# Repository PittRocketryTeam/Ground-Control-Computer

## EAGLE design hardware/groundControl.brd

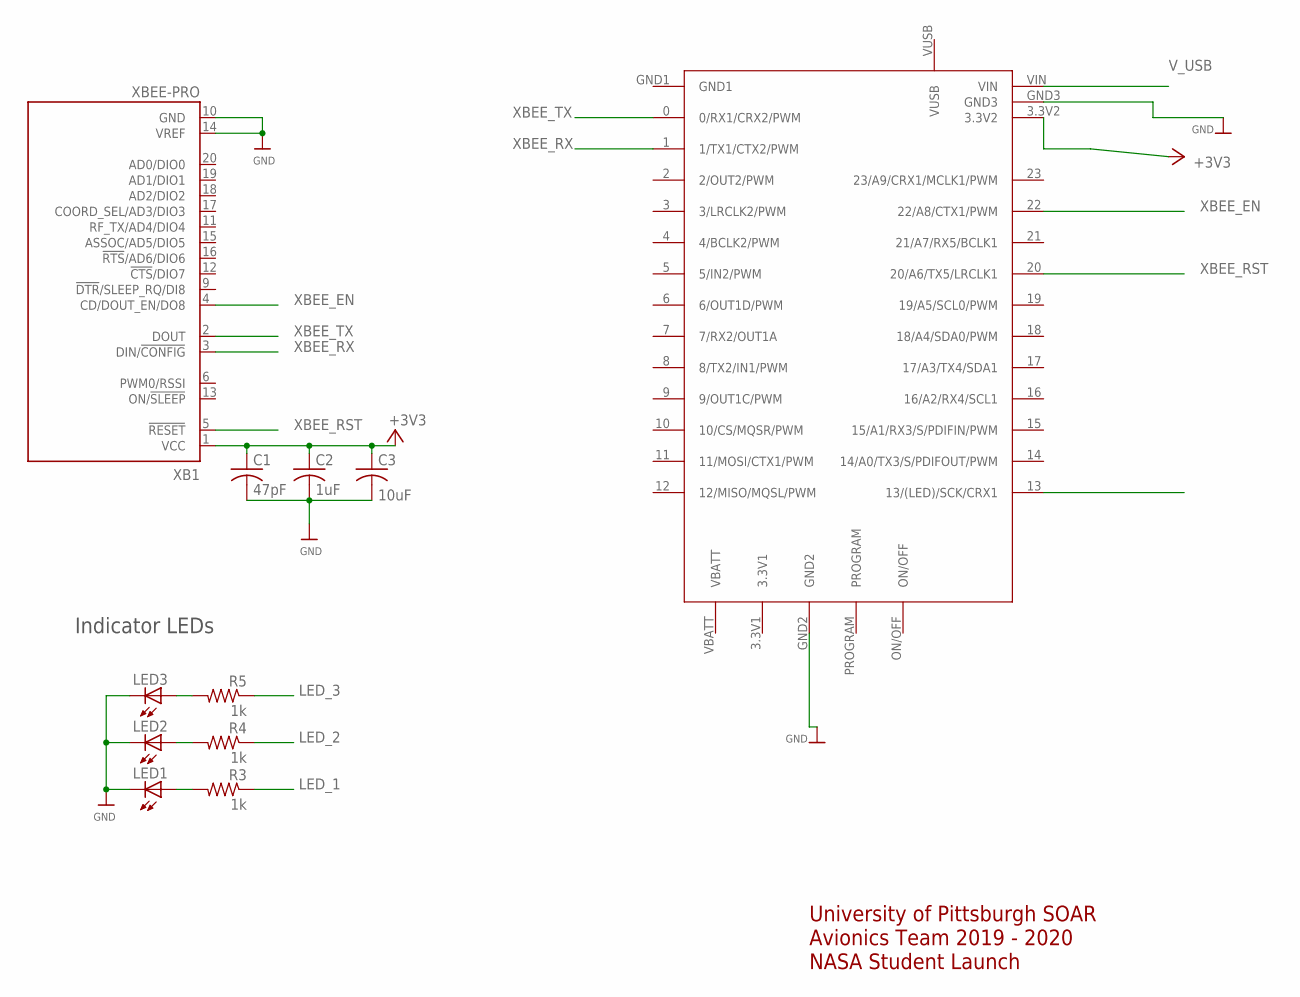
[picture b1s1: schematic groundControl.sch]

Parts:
C1: 47pF; C025-040X050
C2: 1uF; C025-040X050
C3: 10uF; C025-040X050
LED1, LED2, LED3: LED3MM
R3, R4, R5: 1k; 0309/10
U$3: TEENSY4.0
XB1: XBEE-PRO

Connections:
+3V3: C1.1, C2.1, C3.1, U$3.3.3V2, XB1.1 (VCC); also elsewhere on the board
GND: C1.2, C2.2, C3.2, LED1.K (C), LED2.K (C), LED3.K (C), U$3.GND2, U$3.GND3, XB1.10 (GND), XB1.14 (VREF); also elsewhere on the board
LED_1: R3.1; also elsewhere on the board
LED_2: R4.1; also elsewhere on the board
LED_3: R5.1; also elsewhere on the board
unnamed: LED1.A, R3.2
unnamed: LED2.A, R4.2
unnamed: LED3.A, R5.2
XBEE_EN: U$3.22 (22/A8/CTX1/PWM), XB1.4 (CD/DOUT_EN/DO8); also elsewhere on the board
XBEE_RST: U$3.20 (20/A6/TX5/LRCLK1), XB1.5 (!RESET); also elsewhere on the board
XBEE_RX: U$3.1 (1/TX1/CTX2/PWM), XB1.3 (DIN/!CONFIG); also elsewhere on the board
XBEE_TX: U$3.0 (0/RX1/CRX2/PWM), XB1.2 (DOUT); also elsewhere on the board

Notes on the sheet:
Indicator LEDs
University of Pittsburgh SOAR Avionics Team 2019 - 2020 NASA Student Launch

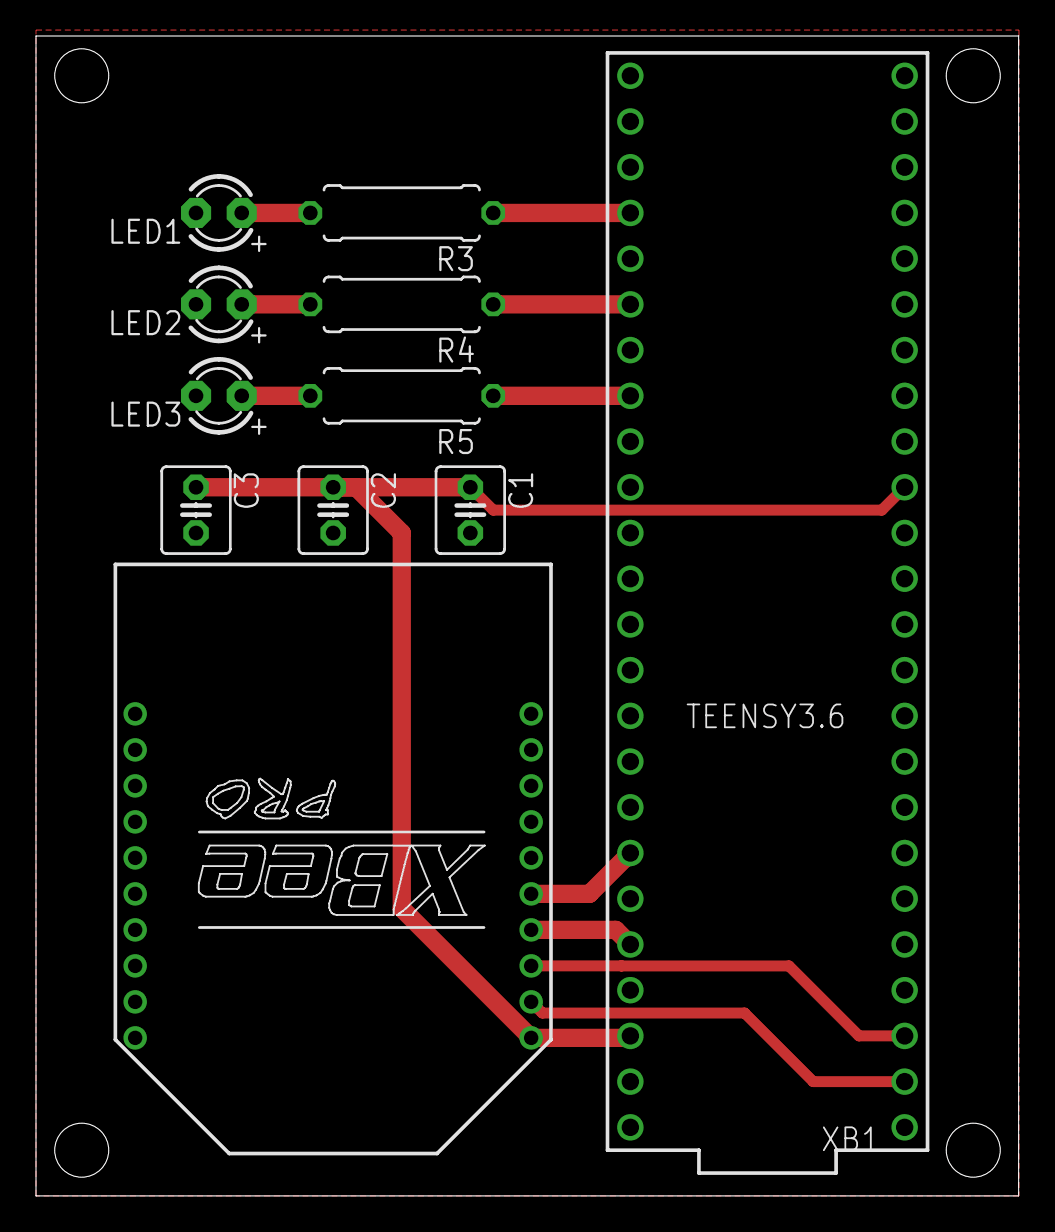
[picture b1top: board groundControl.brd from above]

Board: 2 copper layers, 54.6 x 64.4 mm, 11 parts (0 on the bottom side), 12 nets.

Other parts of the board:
TEENSY3.6: TEENSY_3.6_DIL

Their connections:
+3V3: TEENSY3.6.3.3V, TEENSY3.6.3.3V3; also elsewhere on the board
GND: TEENSY3.6.AGND, TEENSY3.6.GND, TEENSY3.6.GND1; also elsewhere on the board
LED_1: TEENSY3.6.36/A17; also elsewhere on the board
LED_2: TEENSY3.6.38/A19; also elsewhere on the board
LED_3: TEENSY3.6.A21; also elsewhere on the board
XBEE_EN: TEENSY3.6.22/A8; also elsewhere on the board
XBEE_RST: TEENSY3.6.20/A6; also elsewhere on the board
XBEE_RX: TEENSY3.6.1; also elsewhere on the board
XBEE_TX: TEENSY3.6.0; also elsewhere on the board

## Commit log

2019-10-16 initial structure
2019-10-17 added schematic and board
2019-10-18 renamed firmware -> software
2019-12-23 Layout, plotting, and api connections
2019-12-23 Revert "Layout, plotting, and api connections"
    This reverts commit c4b8995673a62c3f15103cc361c99ad2607fadba.
2020-01-02 Teensy Change to 4.0
2020-01-07 Revert "Revert "Layout, plotting, and api connections""
    This reverts commit 68c45e31f6908ff50255d1eba7aef0dfe46e3d48.
2020-01-12 Setup shell for the board
2020-01-13 Outlined SCA data handling and skeleton for functionality based on state
2020-01-13 Error handling the state
2020-01-19 Added serial send and receive for xbees
2020-01-19 Added serial2 connection in setup
2020-01-19 Added extra if statement
2020-01-19 Added counter variable
2020-01-26 Range testing basic update
2020-01-28 Eliminated outdated comments and led code. Edited way to send mode to SCA
2020-01-31 Removed uncessary code and comments
2020-01-31 Moved everything to the left by one tab
2020-02-02 Added changes to display data on new line
2020-02-21 here matt
